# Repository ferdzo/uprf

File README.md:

# uprf
Open Source upconverter
</br>
(Started, but never finished. I swear I will finish it up someday soon)

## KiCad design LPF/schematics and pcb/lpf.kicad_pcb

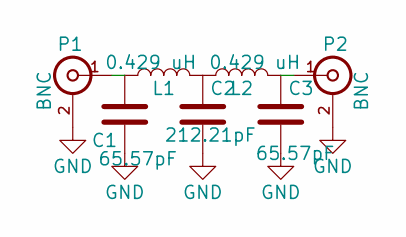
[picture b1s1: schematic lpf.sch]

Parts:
C1, C3: 65.57pF; C_0603
C2: 212.21pF; C_0603
L1, L2: 0.429 uH; R_0603
P1, P2: BNC

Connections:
GND: C1.1, C2.2, C3.2, P1.2 (Ext), P2.2 (Ext)
unnamed: C1.2, L1.1, P1.1 (In)
unnamed: C2.1, L1.2, L2.1
unnamed: C3.1, L2.2, P2.1 (In)

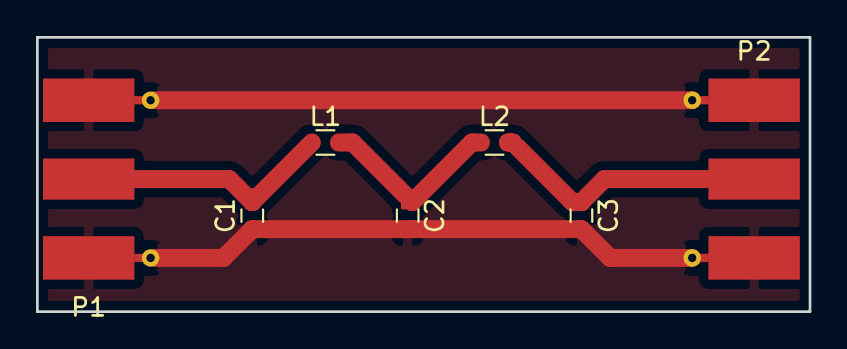
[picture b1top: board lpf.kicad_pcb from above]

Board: 2 copper layers, 42.9 x 15.2 mm, 7 parts (0 on the bottom side), 4 nets.

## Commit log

2017-02-21 Added UpConverter.xml
2017-02-21 Add files via upload
    Plot for the LPF.
2017-03-06 Commit No.1
2017-03-10 schematics and pcb
2017-03-10 asdf
2017-03-14 update1
